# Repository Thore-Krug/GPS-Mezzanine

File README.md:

# GPS-Mezzanine
GPS Mezzanine for 96Boards IoT

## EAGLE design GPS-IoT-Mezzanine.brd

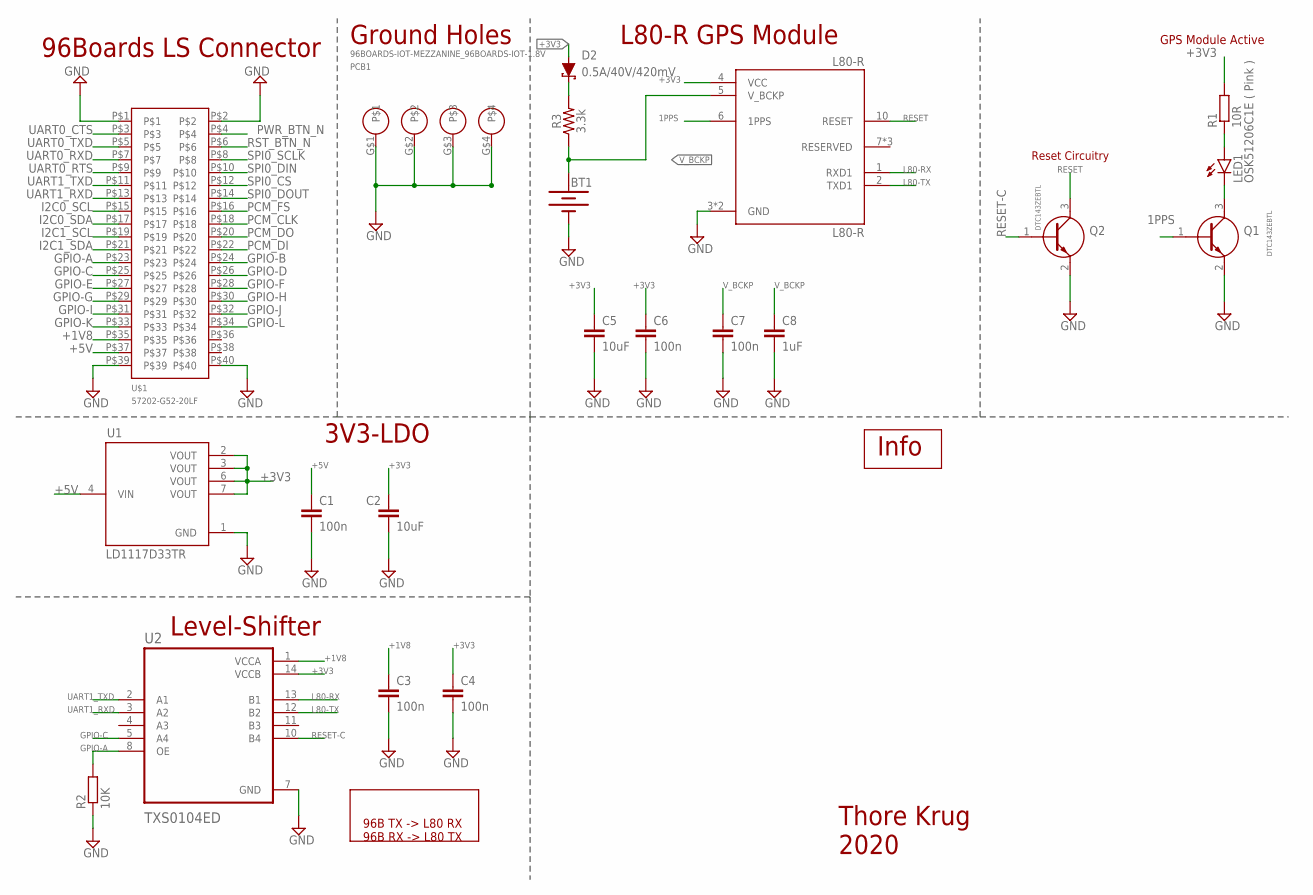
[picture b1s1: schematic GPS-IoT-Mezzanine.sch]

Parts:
BT1: 6.8MM_COIN_CELL; ML414H_IV01E
C1, C3, C4, C6, C7: 100n; C0603
C2, C5: 10uF; C0603
C8: 1uF; C0603
D2: 0.5A/40V/420mV; SOD-323
L80-R: L80-R; XCVR_L80-R
LED1: OSK51206C1E ( Pink ); CHIPLED_1206
PCB1: 96BOARDS-IOT-MEZZANINE_96BOARDS-IOT-1.8V
Q1, Q2: DTC143ZEBTL; SOTFL50P160X85-3N
R1: 10R; R1206
R2: 10K; R0603
R3: 3.3k; 0603
U1: LD1117D33TR; SOIC127P600X175-8N
U2: TXS0104ED; SOIC127P600X175-14N
U$1: 57202-G52-20LF

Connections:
1PPS: L80-R.6 (1PPS), Q1.1 (B)
+1V8: C3.1, U2.1 (VCCA), U$1.P$35
+3V3: C2.1, C4.1, C5.1, C6.1, D2.A, L80-R.4 (VCC), R1.2, U1.2 (VOUT), U1.3 (VOUT), U1.6 (VOUT), U1.7 (VOUT), U2.14 (VCCB)
+5V: C1.1, U1.4 (VIN), U$1.P$37
GND: BT1.-, C1.2, C2.2, C3.2, C4.2, C5.2, C6.2, C7.2, C8.2, L80-R.3 (GND), L80-R.12 (GND), PCB1.G$1, PCB1.G$2, PCB1.G$3, PCB1.G$4, Q1.2 (E), Q2.2 (E), R2.1, U1.1 (GND), U2.7 (GND), U$1.P$1, U$1.P$2, U$1.P$39, U$1.P$40
GPIO-A: R2.2, U2.8 (OE), U$1.P$23
GPIO-B: U$1.P$24
GPIO-C: U2.5 (A4), U$1.P$25
GPIO-D: U$1.P$26
GPIO-E: U$1.P$27
GPIO-F: U$1.P$28
GPIO-G: U$1.P$29
GPIO-H: U$1.P$30
GPIO-I: U$1.P$31
GPIO-J: U$1.P$32
GPIO-K: U$1.P$33
GPIO-L: U$1.P$34
I2C0_SCL: U$1.P$15
I2C0_SDA: U$1.P$17
I2C1_SCL: U$1.P$19
I2C1_SDA: U$1.P$21
L80-RX: L80-R.1 (RXD1), U2.13 (B1)
L80-TX: L80-R.2 (TXD1), U2.12 (B2)
unnamed: LED1.C, Q1.3 (C)
unnamed: LED1.A, R1.1
unnamed: D2.C, R3.2
PCM_CLK: U$1.P$18
PCM_DI: U$1.P$22
PCM_DO: U$1.P$20
PCM_FS: U$1.P$16
PWR_BTN_N: U$1.P$4
RESET: L80-R.10 (RESET), Q2.3 (C)
RESET-C: Q2.1 (B), U2.10 (B4)
RST_BTN_N: U$1.P$6
SPI0_CS: U$1.P$12
SPI0_DIN: U$1.P$10
SPI0_DOUT: U$1.P$14
SPI0_SCLK: U$1.P$8
UART0_CTS: U$1.P$3
UART0_RTS: U$1.P$9
UART0_RXD: U$1.P$7
UART0_TXD: U$1.P$5
UART1_RXD: U2.3 (A2), U$1.P$13
UART1_TXD: U2.2 (A1), U$1.P$11
V_BCKP: BT1.+, C7.1, C8.1, L80-R.5 (V_BCKP), R3.1

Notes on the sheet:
96Boards LS Connector
Ground Holes
L80-R GPS Module
Reset Circuitry
96B TX -> L80 RX 96B RX -> L80 TX
GPS Module Active
3V3-LDO
Level-Shifter
Info
Thore Krug 2020

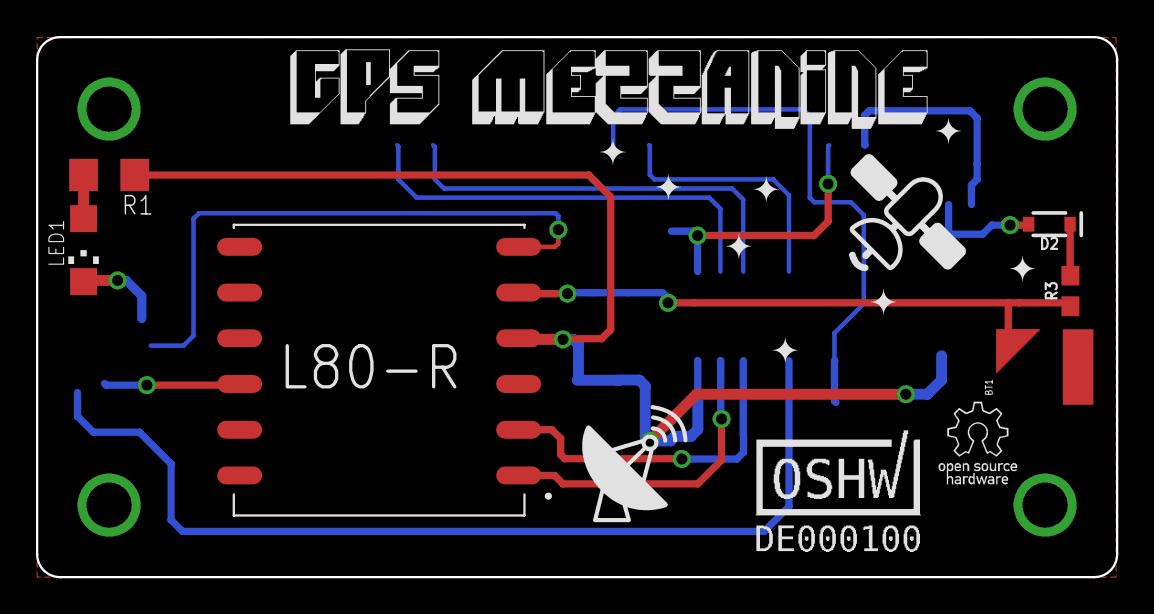
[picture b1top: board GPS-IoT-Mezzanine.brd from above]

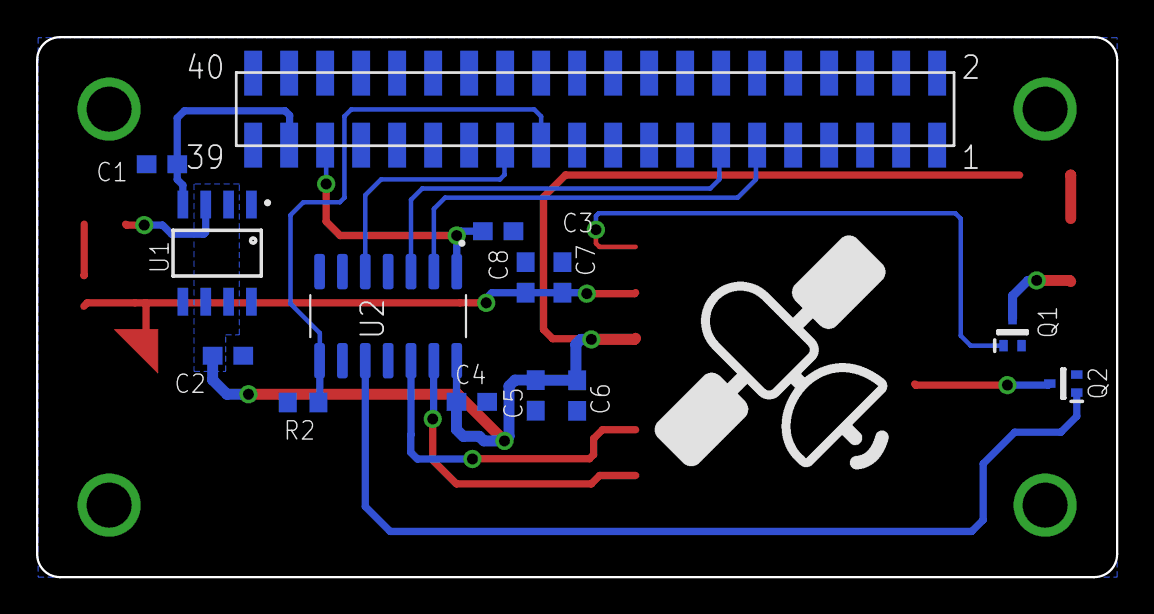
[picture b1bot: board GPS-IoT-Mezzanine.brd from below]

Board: 2 copper layers, 60.0 x 30.0 mm, 21 parts (14 on the bottom side), 17 nets.

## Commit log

2020-11-15 Addition of the GPS Mezzanine
    Added EAGLE, Gerber, libary files.
    Signed off by Thore Krug opensource[at]thorekrug.de
2020-11-15 Create README.md
    Signed off by Thore Krug opensource@thorekrug.de
2020-11-16 Create LICENSE
    Signed off by Thore Krug opensource[at]thorekrug.de
2020-11-17 Improvements to the mezzanine
    added keepout for the antenna, improved silkscreen on top layer, improved poer traces to the Level shifter IC.
    Signed off by Thore Krug opensource[at]thorekrug.de
2020-11-20 Board Update + BOM
    Added Round Corner to make the Board more pleasing to the eye, added current limiting resistor for the pink status LED indication 1PPS ( 1 Puls per Second ) created by the L80-R GPS Module. Added BOM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
    Signed off by: Thore Krug opensource[at]thorekrug.de
2021-01-18 Updated PCB
    Update of PCB ( Disable thermal relief for the mounting holes )
    Signed off by: Thore Krug opensource[at]thorekrug.de

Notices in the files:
parts and their libraries:
SparkFun-Batteries: Licensing: Creative Commons ShareAlike 4.0 International - https://creativecommons.org/licenses/by-sa/4.0
